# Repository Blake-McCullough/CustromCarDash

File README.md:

# Custom Car Dash: 2013 Subaru Impreza

Built for a 2013 Impreza, but the CAN decodes are per-car **vehicle profiles** (`pi/vehicles/`), picked in
Settings → VEHICLE. There's also a starter Mazda RX-8 profile (unverified) and a generic OBD-II one for any car.

| Folder | What it is |
|---|---|
| `docs/CAN_DECODES.md` | What each CAN message on the car means (gear, speed, steering, lights…), with evidence from the logs. |
| `pi/vehicles/` | One JSON per car: its CAN decodes, bitrate, redline, weight and gear ratios. Copy one to add a car. |
| `pi/` | **The dash.** Raspberry Pi 5 + Waveshare RS485 CAN HAT: 3D wireframe car, gauges, G-meter, graphs, CAN bus viewer. One-command installer, boots straight into the dash. See `pi/README.md`. |
| `esp32canlogger/` | Standalone ESP32 + CAN Pal logger: phone over Wi-Fi, live CAN view, record + download CSV. |
| `esp32_canpal_slcan/` | Optional: ESP32 + CAN Pal as a USB CAN adapter for the Pi (instead of the HAT). Use `pi/setup_can_esp32_bridge.sh`. |

## Safety rules for this project
- Everything connects **listen-only**. The Pi HAT is brought up with `listen-only on`. The ESP32
  boards run TWAI listen-only, and the CAN Pal has **SLNT tied to 3V3**.
- **Never** connect OBD pin 16 (+12 V, red) to any board. Tape off unused pigtail wires.
- Termination **off** on every board (the car's bus is already terminated).
- Don't use the SN65HVD230 breakout on the car: it has no silent pin.
- First connection to the car: engine off, key to ON, check the warning lights stay normal before starting.

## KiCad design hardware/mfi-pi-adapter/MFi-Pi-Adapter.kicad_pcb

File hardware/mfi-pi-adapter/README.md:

# MFi 3.0 → Raspberry Pi adapter board (MFI343S00177)

A 16 × 11.6 mm two-layer board that carries the Apple Auth 3.0 chip (MFI343S00177, XDFN-8 2×3 mm). It either plugs straight onto **Pi header pins 1–6** or gets wired to the Pi through a **4-pin header**. It works on the Pi 4 and Pi 5 with LIVI.

## Files
| File | What it's for |
|---|---|
| `MFi-Pi-Adapter-Gerbers-JLCPCB.zip` | Upload this to JLCPCB (or PCBWay, etc.) to order the bare board |
| `gerbers/` | The same Gerber and drill files, unzipped |
| `MFi-Pi-Adapter-preview.png` | What the board looks like, both sides |
| `MFi-Pi-Adapter.kicad_pcb` | KiCad file, if you want to change anything |
| `build_board.py` | Script that generated the board (KiCad 7 Python) |

### `assembly/` (parts lists)
| File | What it's for |
|---|---|
| `BOM-full.csv` | Every part, with manufacturer and LCSC numbers, for checking or hand assembly |
| `JLCPCB-BOM.csv` | JLCPCB assembly BOM: U1 + C1 (R1/R2 left out = not placed) |
| `JLCPCB-BOM-with-pullups.csv` | The same, plus R1/R2 |
| `JLCPCB-CPL.csv` | Component placement in the Gerbers' own coordinates (mm; board spans X 0…16, Y 0…−11.6, so Y is negative) |

If you order JLCPCB assembly: in the placement preview, the **chip's pin-1 dot must sit on the white silk dot**, top-left of U1, and the body must be **wider than tall** (3 × 2 mm). The CPL sets U1 to **270°** because JLCPCB's model for this part showed up 90° off at 0°. Still check it in the preview: their library can change. J1/J2 aren't in the assembly files: hand-solder them.

To regenerate it: `python3 build_board.py` (needs KiCad 7 and the `kicad-footprints` library), then open the `.kicad_pcb` in KiCad, run DRC, and plot Gerbers.

## Ordering (bare PCB, no assembly)
- Upload the zip. Settings: **2 layers, FR-4, 1.6 mm, qty 5**. Leave everything else at the defaults.
- **Surface finish:** the cheapest lead-free HASL works. **ENIG** gives flatter pads for the tiny chip if you're willing to pay a bit more.
- **Don't** add SMT assembly. You fit the parts yourself.
- Design rules used: 0.15 mm minimum clearance, 0.2 mm minimum track, 0.3 mm via drill. All are within JLCPCB's standard 2-layer limits.

## Parts
| Ref | Part | Notes |
|---|---|---|
| U1 | MFI343S00177 (XDFN-8 2×3 mm) | Your AliExpress chip |
| C1 | 100 nF ceramic, **0805** | Required: decoupling, right next to the VCC pin |
| R1, R2 | 10 kΩ, **0805** | **Optional.** The Pi already has pull-ups on pins 3/5. Only fit these if you wire J2 to a different, software I²C bus |
| J1 | 2×3 **female** header, 2.54 mm | Soldered on the **BOTTOM** (the side marked "SOCKET HERE"). Plugs onto Pi pins 1–6 |
| J2 | 1×4 male header, 2.54 mm | Optional. Use it instead of J1 to wire the board to the Pi with jumper wires |

Fit **either J1 or J2**, not both.

## Pin map (checked against the datasheet)
| Chip pad | Signal | Board | Pi header |
|---|---|---|---|
| 8 | VCC | J1.1 / J2 "3V3" | **Pin 1 (3.3 V)** |
| 5 | SDA | J1.3 / J2 "SDA" | Pin 3 (GPIO 2) |
| 6 | SCL | J1.5 / J2 "SCL" | Pin 5 (GPIO 3) |
| 1, 4, 7, centre pad | GND | J1.6 / J2 "GND" | Pin 6 |
| 2, 3 | NC | not connected | — |
| — | — | J1.2, J1.4 | Pi 5 V pins: **deliberately not connected** |

## Assembly order
1. **Chip first.** Put a thin smear of solder paste on the 8 pads, plus a small amount on the centre pad. Placing it is optional: the datasheet allows the centre pad to be left unsoldered, and the board doesn't need it for ground. Line up the **pin-1 dot on the chip with the white dot on the board**, top-left of the chip. Heat on the hot plate until the paste goes shiny and the chip settles into place on its own.
   - The pads are 0.25 mm longer than Apple's spec, extending outward, so you can see the joints and touch them up with a fine iron tip.
2. **Inspect** under magnification for solder bridges, especially between pads 5–8. Pads 2 and 3 must **not** be bridged to anything.
3. **C1**, then R1/R2 if you need them.
4. **J1 on the bottom**, or J2 on either side.
5. **Before the Pi:** with a multimeter, check 3V3 to GND on J2 (or J1 pins 1 and 6). It must **not** read as a short.

## Fitting it the right way round (important)
Plugged in backwards, it puts **5 V onto SDA and SCL** and will kill the chip.
- The **square pad of J1** goes on **Pi pin 1** (3.3 V).
- The **outer column of J1 (pins 2, 4, 6, the "5V row")** faces the **edge of the Pi**. The rest of the board sits over the Pi.
- The board also sits over Pi pins 7 and 8, but doesn't connect to them.

### With your Waveshare CAN HAT
The HAT covers pins 1–6, so either:
- Use a **stacking header** (extra-long pins) under the CAN HAT and plug J1 onto the pins sticking out the top. Check that nothing tall on the HAT is in the way.
- **Or** fit J2 and run 4 jumper wires to Pi pins 1 (3V3), 6 (GND), 3 (SDA) and 5 (SCL). You can also solder the wires to the HAT's pass-through pads. Check the HAT doesn't use GPIO 2/3.

## Software
`/boot/firmware/config.txt`:
```
dtparam=i2c_arm=on
```
LIVI `config.json`:
```json
{ "carPlayMfiI2cBus": 1, "carPlayMfiPowerGpio": -1 }
```
Test once, with LIVI stopped: `sudo i2cdetect -y 1` should show **10**. Then start LIVI and connect your iPhone. A working CarPlay connection is what proves the chip is genuine.

## Design notes
- Land pattern from Apple's Auth 3.0 CP datasheet (Table 67-2): 0.50 mm pitch, 0.30 mm pads, rows 2.90 mm apart centre to centre. Pads lengthened to 1.15 mm, outward only.
- Centre pad reduced to 1.2 × 1.1 mm to leave 0.4 mm clearance to the signal pads, which lowers the risk of bridges when hand-reflowing.
- Ground pour on the bottom layer. Ground pads 1, 4 and 7 are tied together on top as well.
- KiCad design check: 0 clearance errors, 0 unconnected pads.

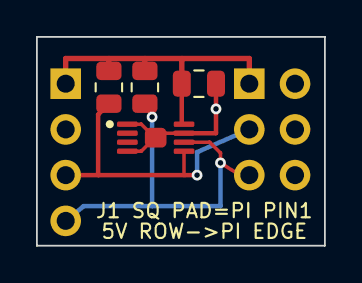
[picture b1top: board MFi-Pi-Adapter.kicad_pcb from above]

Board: 2 copper layers, 16.0 x 11.6 mm, 6 parts (0 on the bottom side), 4 nets.

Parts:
C1: 100nF; C_0805_2012Metric
J1: Pi header pins 1-6 (2x3 female socket, BOTTOM sid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; PinHeader_2x03_P2.54mm_Vertical
J2: Wire header 3V3/GND/SDA/SCL; PinHeader_1x04_P2.54mm_Vertical
R1, R2: 10k (optional); R_0805_2012Metric
U1: MFI343S00177 (XDFN-8 2x3); XDFN-8_2x3mm_P0.5mm_HandSolder

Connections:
+3V3: C1.1, J1.1, J2.1, R1.2, R2.2, U1.8
GND: C1.2, J1.6, J2.2, U1.1, U1.4, U1.7, U1.9
SCL: J1.5, J2.4, R2.1, U1.6
SDA: J1.3, J2.3, R1.1, U1.5

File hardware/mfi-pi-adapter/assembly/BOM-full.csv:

Designator,Qty,Value,Package,Manufacturer part,LCSC/JLCPCB part #,Fit?,Notes
U1,1,MFI343S00177-L,XDFN-8 2x3mm P0.5mm,Microchip MFI343S00177-L,C33770534,Yes,Apple Auth 3.0 chip. Pin-1 dot = white silk dot (top-left). Or use your AliExpress chip
C1,1,100nF 50V X7R,0805,YAGEO CC0805KRX7R9BB104,C49678,Yes,"Decoupling, required. JLCPCB Basic part"
"R1,R2",2,10k 1%,0805,UNI-ROYAL 0805W8F1002T5E,C17414,Optional,I2C pull-ups. NOT needed on Pi pins 3/5 (Pi has 1.8k). JLCPCB Basic part
J1,1,2x3 female header 2.54mm,THT 2x3,generic,,Hand solder,Solder on the BOTTOM side. Plugs onto Pi pins 1-6. Fit J1 OR J2
J2,1,1x4 male header 2.54mm,THT 1x4,generic,,"Optional, hand solder",Wire header 3V3/GND/SDA/SCL. Fit J1 OR J2
